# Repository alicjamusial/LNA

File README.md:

# Lynx - LNA with filter for 400-440 MHz

### ◾ About the project

**Lynx** is an LNA with a filter with two SMA connectors. It was designed for 400-400 MHz (UHF satellite amateur band) by default, but by changing components' values it can be tuned to every chosen frequency. It contains the amplifier (with PGA-103+ as the main component) and the bandpass Chelbyshev filter (shunt first, 2nd order).
 
Gerber files for version 2.0 of Lynx is available [in the releases section](https://github.com/alicjamusial/LNA/releases/tag/release-2.0.0). 

The board was designed using [KiCad](https://kicad.org/) (version: `5.99.0-7233-g6a28d6af27`).

### ◾ Usage
- **Very important!** Order PCB with **0.6mm** thickness and 1oz copper weight.
- Lynx requires connection of 5V and GND.
- It would be best to connect Lynx as close to the antenna as possible.

### ◾ Parameters
According to the measurements, in range 400-440 MHz Lynx should provide gain around 16-20 dB.

### ◾ License
Lynx is available on Creative Commons Attribution Share Alike 4.0 International license (more in [license file](LICENSE.txt)). You are free to use it, modify it and produce as many of your own boards as you need :)

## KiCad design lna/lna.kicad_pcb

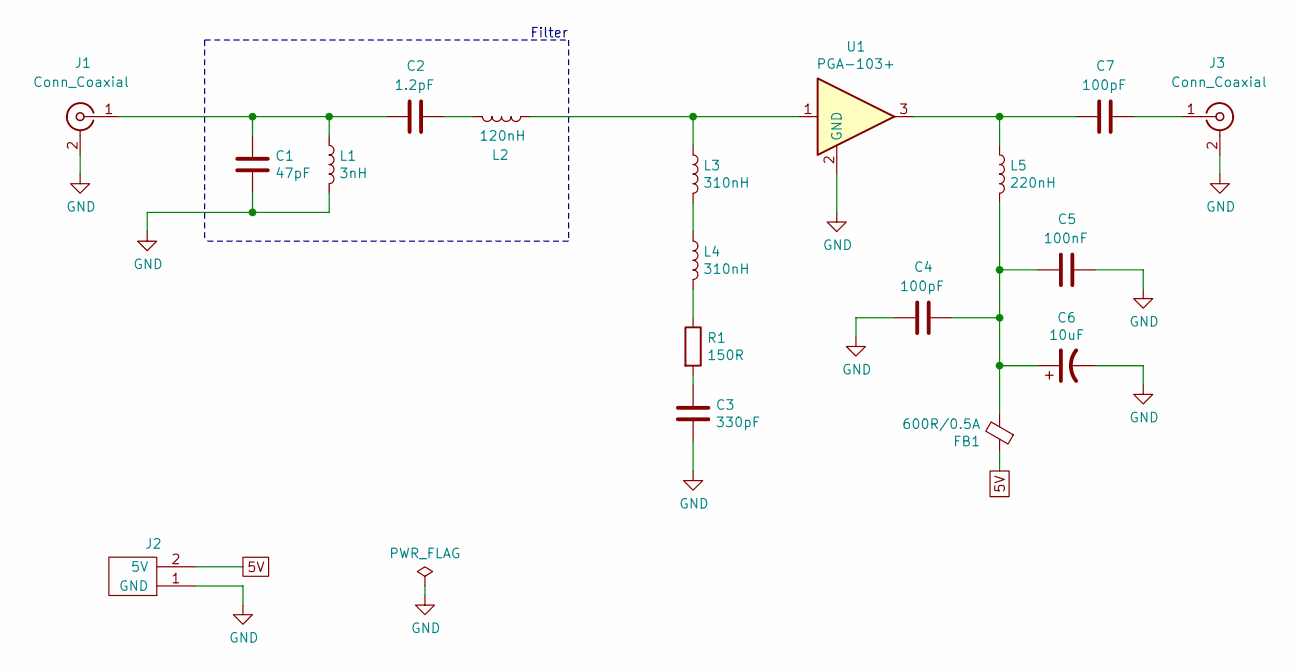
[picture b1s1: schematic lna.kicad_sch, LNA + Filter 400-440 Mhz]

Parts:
C1: 47pF; C_0603_1608Metric
C2: 1.2pF; C_0603_1608Metric
C3: 330pF; C_0603_1608Metric
C4, C7: 100pF; C_0603_1608Metric
C5: 100nF; C_0603_1608Metric
C6: 10uF; CP_EIA-3216-18_Kemet-A
FB1: 600R/0.5A; Murata-BLM18-0.15-t0.8-0-0-IPC_A
J1, J3: Conn_Coaxial; SMA_Amphenol_132289_EdgeMount
J2: V5-GND; PinHeader_1x02_P2.54mm_Vertical
L1: 3nH; L_0805_2012Metric
L2: 120nH; L_0805_2012Metric
L3, L4: 310nH; L_0805_2012Metric
L5: 220nH; L_0805_2012Metric
R1: 150R; R_0603_1608Metric
U1: PGA-103+; SOT-89-3

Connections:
5V: FB1.1, J2.2 (5V)
GND: C1.2, C3.2, C4.1, C5.2, C6.2, J1.2 (Ext), J2.1 (GND), J3.2 (Ext), L1.2, U1.2 (GND)
unnamed: C1.1, C2.1, J1.1 (In), L1.1
unnamed: C2.2, L2.2
unnamed: C3.1, R1.2
unnamed: C4.2, C5.1, C6.1, FB1.2, L5.2
unnamed: C7.1, L5.1, U1.3
unnamed: C7.2, J3.1 (In)
unnamed: L2.1, L3.1, U1.1
unnamed: L3.2, L4.1
unnamed: L4.2, R1.1

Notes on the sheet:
Filter

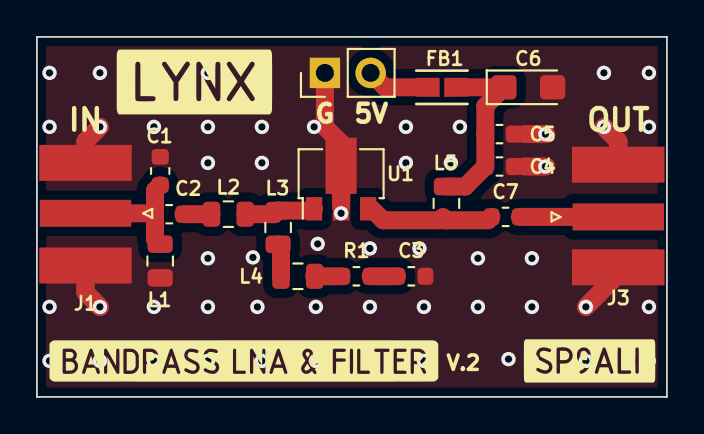
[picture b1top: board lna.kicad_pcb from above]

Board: 2 copper layers, 35.0 x 20.0 mm, 18 parts (0 on the bottom side), 11 nets.

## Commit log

2021-07-14 Repo init
2021-07-14 Start LNA project
2021-07-15 Schematics
2021-07-15 Footprints
2021-07-15 PCB part 1
2021-07-15 Routes
2021-07-15 Add ferrite bead
2021-07-15 Final v1
2021-07-15 Add some fixes
2021-07-15 Refill zones
2021-07-15 Solid zones
2021-07-15 Images
2021-07-17 LNA images
2021-07-17 Add so many holes
2021-07-17 Add 3D models for SMA
2021-08-16 Gerbers
2021-08-16 Gerbers v2
2021-11-21 Cleanup
2021-11-21 Cleanup libraries
2021-11-21 Remove not needed files
2021-11-21 Add proper values of components & update readme
2021-11-21 Add readme
2021-11-21 Add proper component value
2021-11-21 Add schematics
2021-11-22 Add info about copper
2021-12-07 Fix README
